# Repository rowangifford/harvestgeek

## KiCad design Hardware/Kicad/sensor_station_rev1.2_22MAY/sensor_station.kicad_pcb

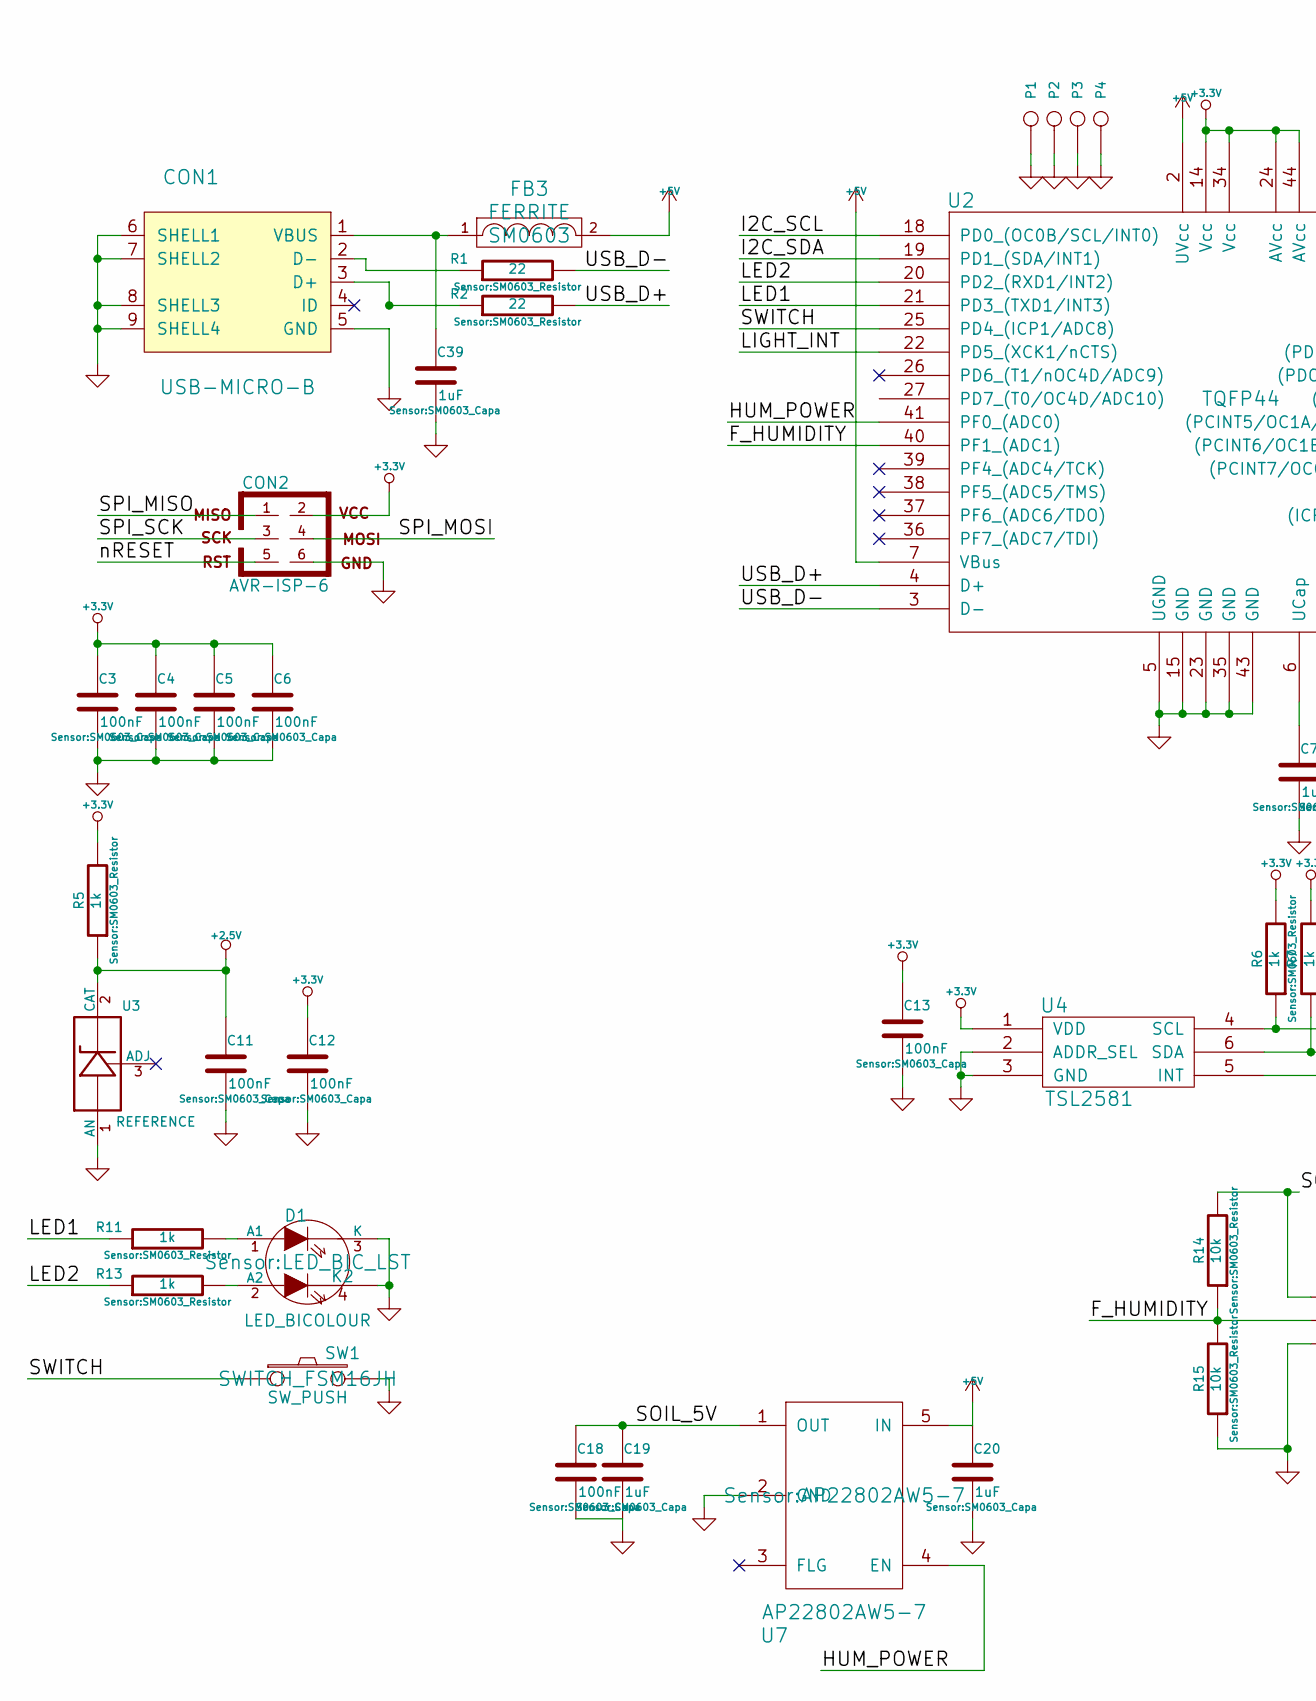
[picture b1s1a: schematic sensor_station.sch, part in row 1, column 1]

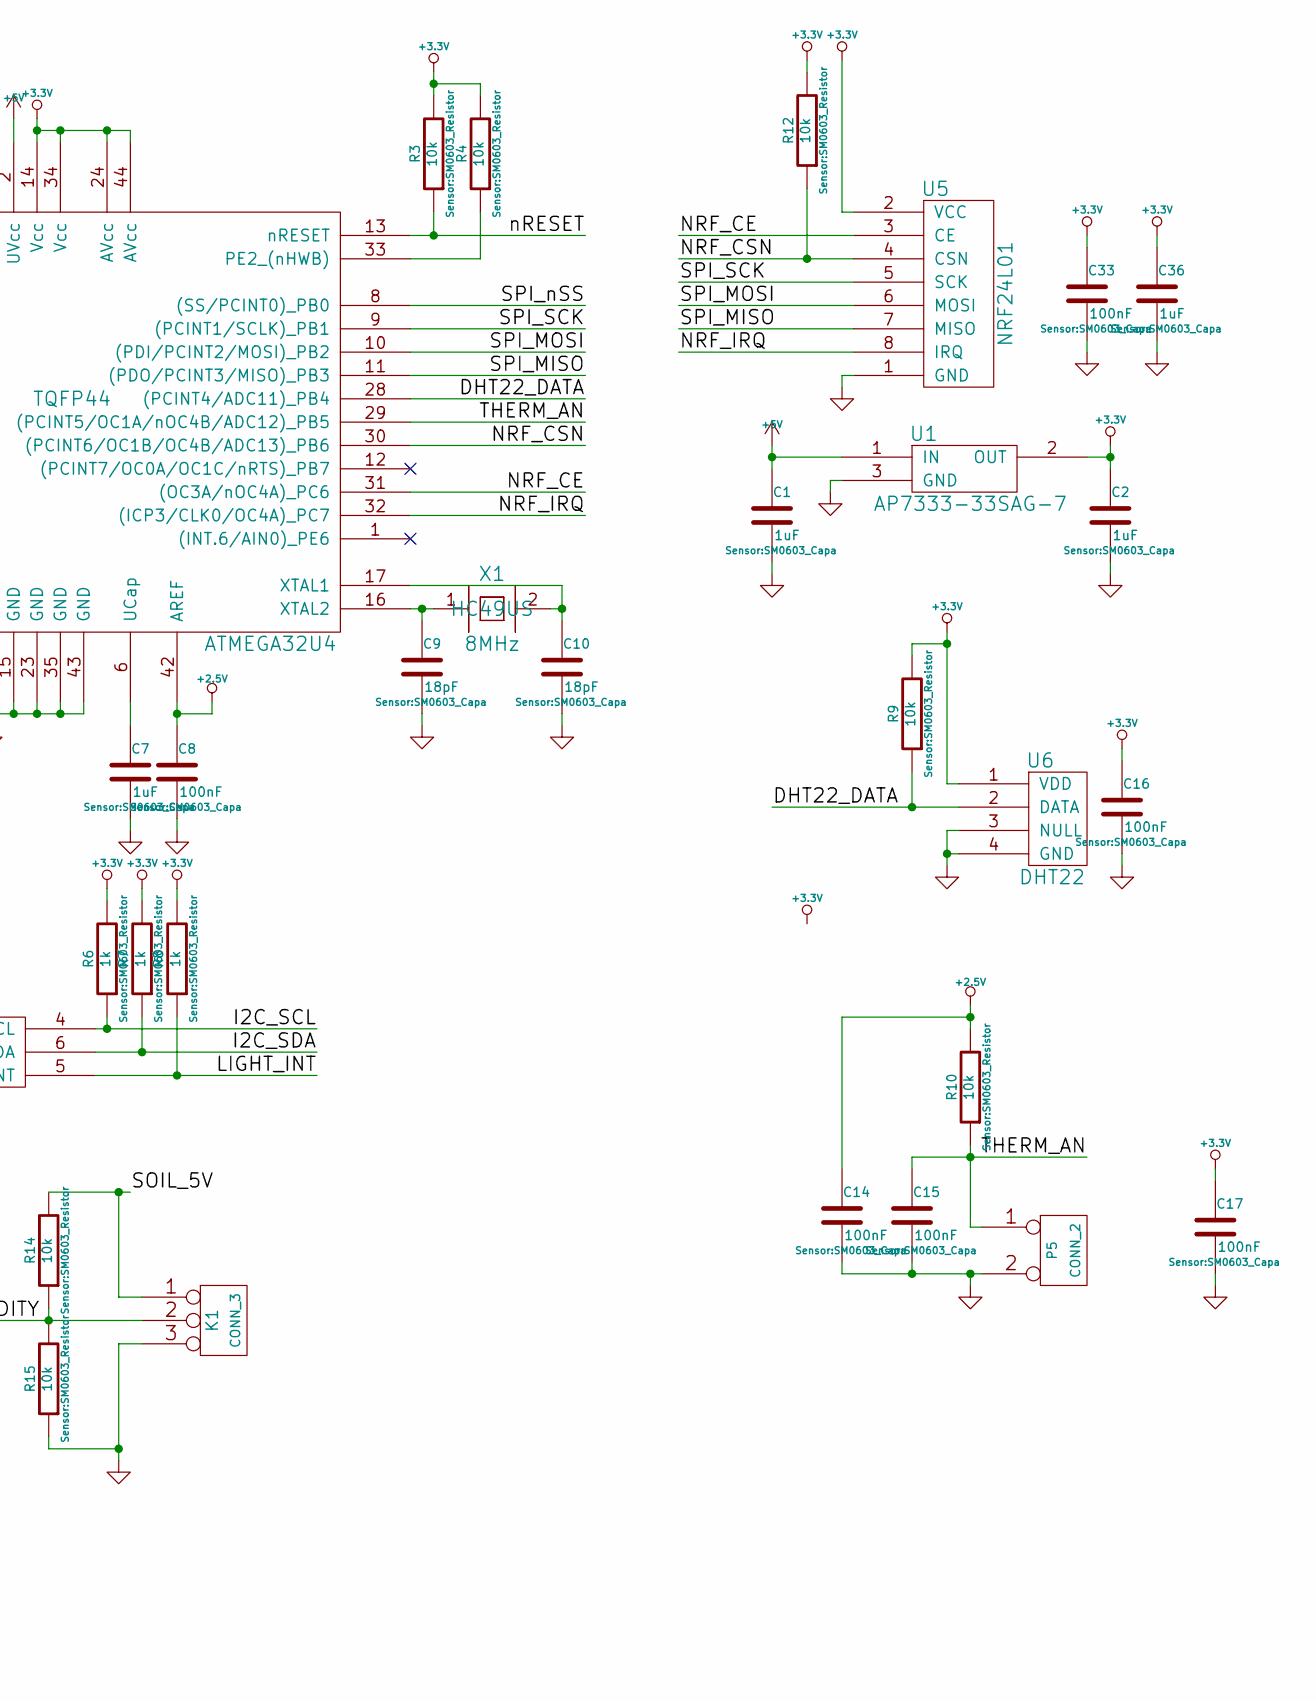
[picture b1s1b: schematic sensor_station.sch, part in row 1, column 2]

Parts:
C1, C2, C7, C19, C20, C36, C39: 1uF; SM0603_Capa
C3, C4, C5, C6, C8, C11, C12, C13, C14, C15, C16, C17, C18, C33: 100nF; SM0603_Capa
C9, C10: 18pF; SM0603_Capa
CON1: USB-MICRO-B; con_microusb_10103594
CON2: AVR-ISP-6; pin_array_3x2
D1: LED_BICOLOUR; LED_BIC_LST
FB3: FERRITE; SM0603
K1: CONN_3; CON_3_weidmuller
P1, P2, P3, P4: CONN_1; HOLE_FIX_HAMMOND
P5: CONN_2; CON_2_weidmuller
R1, R2: 22; SM0603_Resistor
R3, R4, R9, R10, R12, R14, R15: 10k; SM0603_Resistor
R5, R6, R7, R8, R11, R13: 1k; SM0603_Resistor
SW1: SW_PUSH; SWITCH_FSM16JH
U1: AP7333-33SAG-7; SOT23
U2: ATMEGA32U4; TQFP44
U3: REFERENCE; TO92F
U4: TSL2581; 6-WDFN
U5: NRF24L01
U6: DHT22
U7: AP22802AW5-7
X1: 8MHz; HC49US

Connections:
+2.5V: C8.1, C11.1, C14.1, R5.1, R10.2, U2.42 (AREF), U3.2 (CAT)
+3.3V: C2.1, C3.1, C4.1, C5.1, C6.1, C12.1, C13.1, C16.1, C17.1, C33.1, C36.1, CON2.2, R3.2, R4.2, R5.2, R6.2, R7.2, R8.2, R9.2, R12.2, U1.2 (OUT), U2.14 (Vcc), U2.24 (AVcc), U2.34 (Vcc), U2.44 (AVcc), U4.1 (VDD), U5.2 (VCC), U6.1 (VDD)
+5V: C1.1, C20.1, FB3.2, U1.1 (IN), U2.2 (UVcc), U2.7 (VBus), U7.5 (IN)
/DHT22_DATA: R9.1, U2.28 ((PCINT4/ADC11)_PB4), U6.2 (DATA)
/F_HUMIDITY: K1.2 (PM), R14.1, R15.2, U2.40 (PF1_(ADC1))
/HUM_POWER: U2.41 (PF0_(ADC0)), U7.4 (EN)
/I2C_SCL: R6.1, U2.18 (PD0_(OC0B/SCL/INT0)), U4.4 (SCL)
/I2C_SDA: R7.1, U2.19 (PD1_(SDA/INT1)), U4.6 (SDA)
/LED1: R11.1, U2.21 (PD3_(TXD1/INT3))
/LED2: R13.1, U2.20 (PD2_(RXD1/INT2))
/LIGHT_INT: R8.1, U2.22 (PD5_(XCK1/nCTS)), U4.5 (INT)
/NRF_CE: U2.31 ((OC3A/nOC4A)_PC6), U5.3 (CE)
/NRF_CSN: R12.1, U2.30 ((PCINT6/OC1B/OC4B/ADC13)_PB6), U5.4 (CSN)
/NRF_IRQ: U2.32 ((ICP3/CLK0/OC4A)_PC7), U5.8 (IRQ)
/SOIL_5V: C18.1, C19.1, K1.1, R14.2, U7.1 (OUT)
/SPI_MISO: CON2.1, U2.11 ((PDO/PCINT3/MISO)_PB3), U5.7 (MISO)
/SPI_MOSI: CON2.4, U2.10 ((PDI/PCINT2/MOSI)_PB2), U5.6 (MOSI)
/SPI_SCK: CON2.3, U2.9 ((PCINT1/SCLK)_PB1), U5.5 (SCK)
/SPI_nSS: U2.8 ((SS/PCINT0)_PB0)
/SWITCH: SW1.1, U2.25 (PD4_(ICP1/ADC8))
/THERM_AN: C15.1, P5.1, R10.1, U2.29 ((PCINT5/OC1A/nOC4B/ADC12)_PB5)
/USB_D+: R2.2, U2.4 (D+)
/USB_D-: R1.2, U2.3 (D-)
/nRESET: CON2.5, R3.1, U2.13 (nRESET)
GND: C1.2, C2.2, C3.2, C4.2, C5.2, C6.2, C7.2, C8.2, C9.2, C10.2, C11.2, C12.2, C13.2, C14.2, C15.2, C16.2, C17.2, C18.2, C19.2, C20.2, C33.2, C36.2, C39.2, CON1.5 (GND), CON1.6 (SHELL1), CON1.7 (SHELL2), CON1.8 (SHELL3), CON1.9 (SHELL4), CON2.6, D1.3 (K), D1.4 (K2), K1.3, P1.1, P2.1, P3.1, P4.1, P5.2 (PM), R15.1, SW1.2, U1.3 (GND), U2.5 (UGND), U2.15 (GND), U2.23 (GND), U2.35 (GND), U2.43 (GND), U3.1 (AN), U4.2 (ADDR_SEL), U4.3 (GND), U5.1 (GND), U6.3 (NULL), U6.4 (GND), U7.2 (GND); also elsewhere on the board
unnamed: C7.1, U2.6 (UCap)
unnamed: C9.1, U2.16 (XTAL2), X1.1
unnamed: C10.1, U2.17 (XTAL1), X1.2
unnamed: C39.1, CON1.1 (VBUS), FB3.1
unnamed: CON1.2 (D-), R1.1
unnamed: CON1.3 (D+), R2.1
unnamed: D1.1 (A1), R11.2
unnamed: D1.2 (A2), R13.2
unnamed: R4.1, U2.33 (PE2_(nHWB))

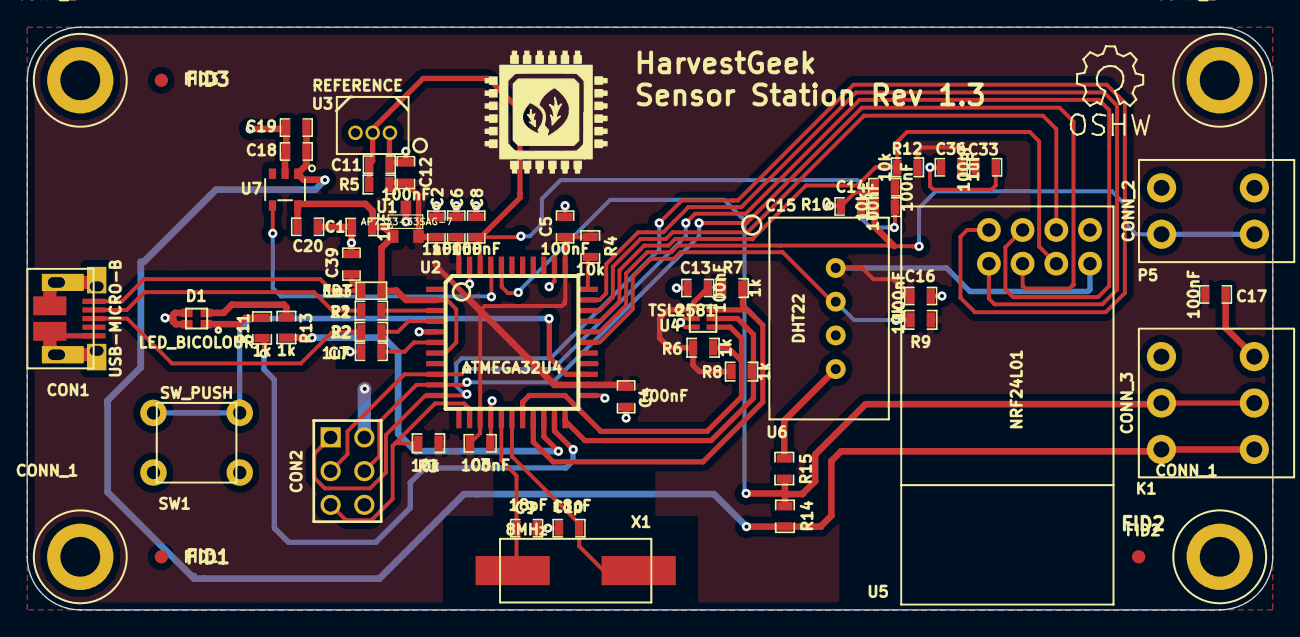
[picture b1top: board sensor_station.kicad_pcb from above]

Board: 2 copper layers, 93.9 x 43.9 mm, 60 parts (0 on the bottom side), 33 nets.

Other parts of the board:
Fiducial: FID3; Fiducial
Fiducial#2: FID2; Fiducial
Fiducial#3: FID1; Fiducial
P1#2, P1#3, P1#4: CONN_1; HOLE_FIX_HAMMOND

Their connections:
GND: P1#2.1, P1#3.1, P1#4.1; also elsewhere on the board

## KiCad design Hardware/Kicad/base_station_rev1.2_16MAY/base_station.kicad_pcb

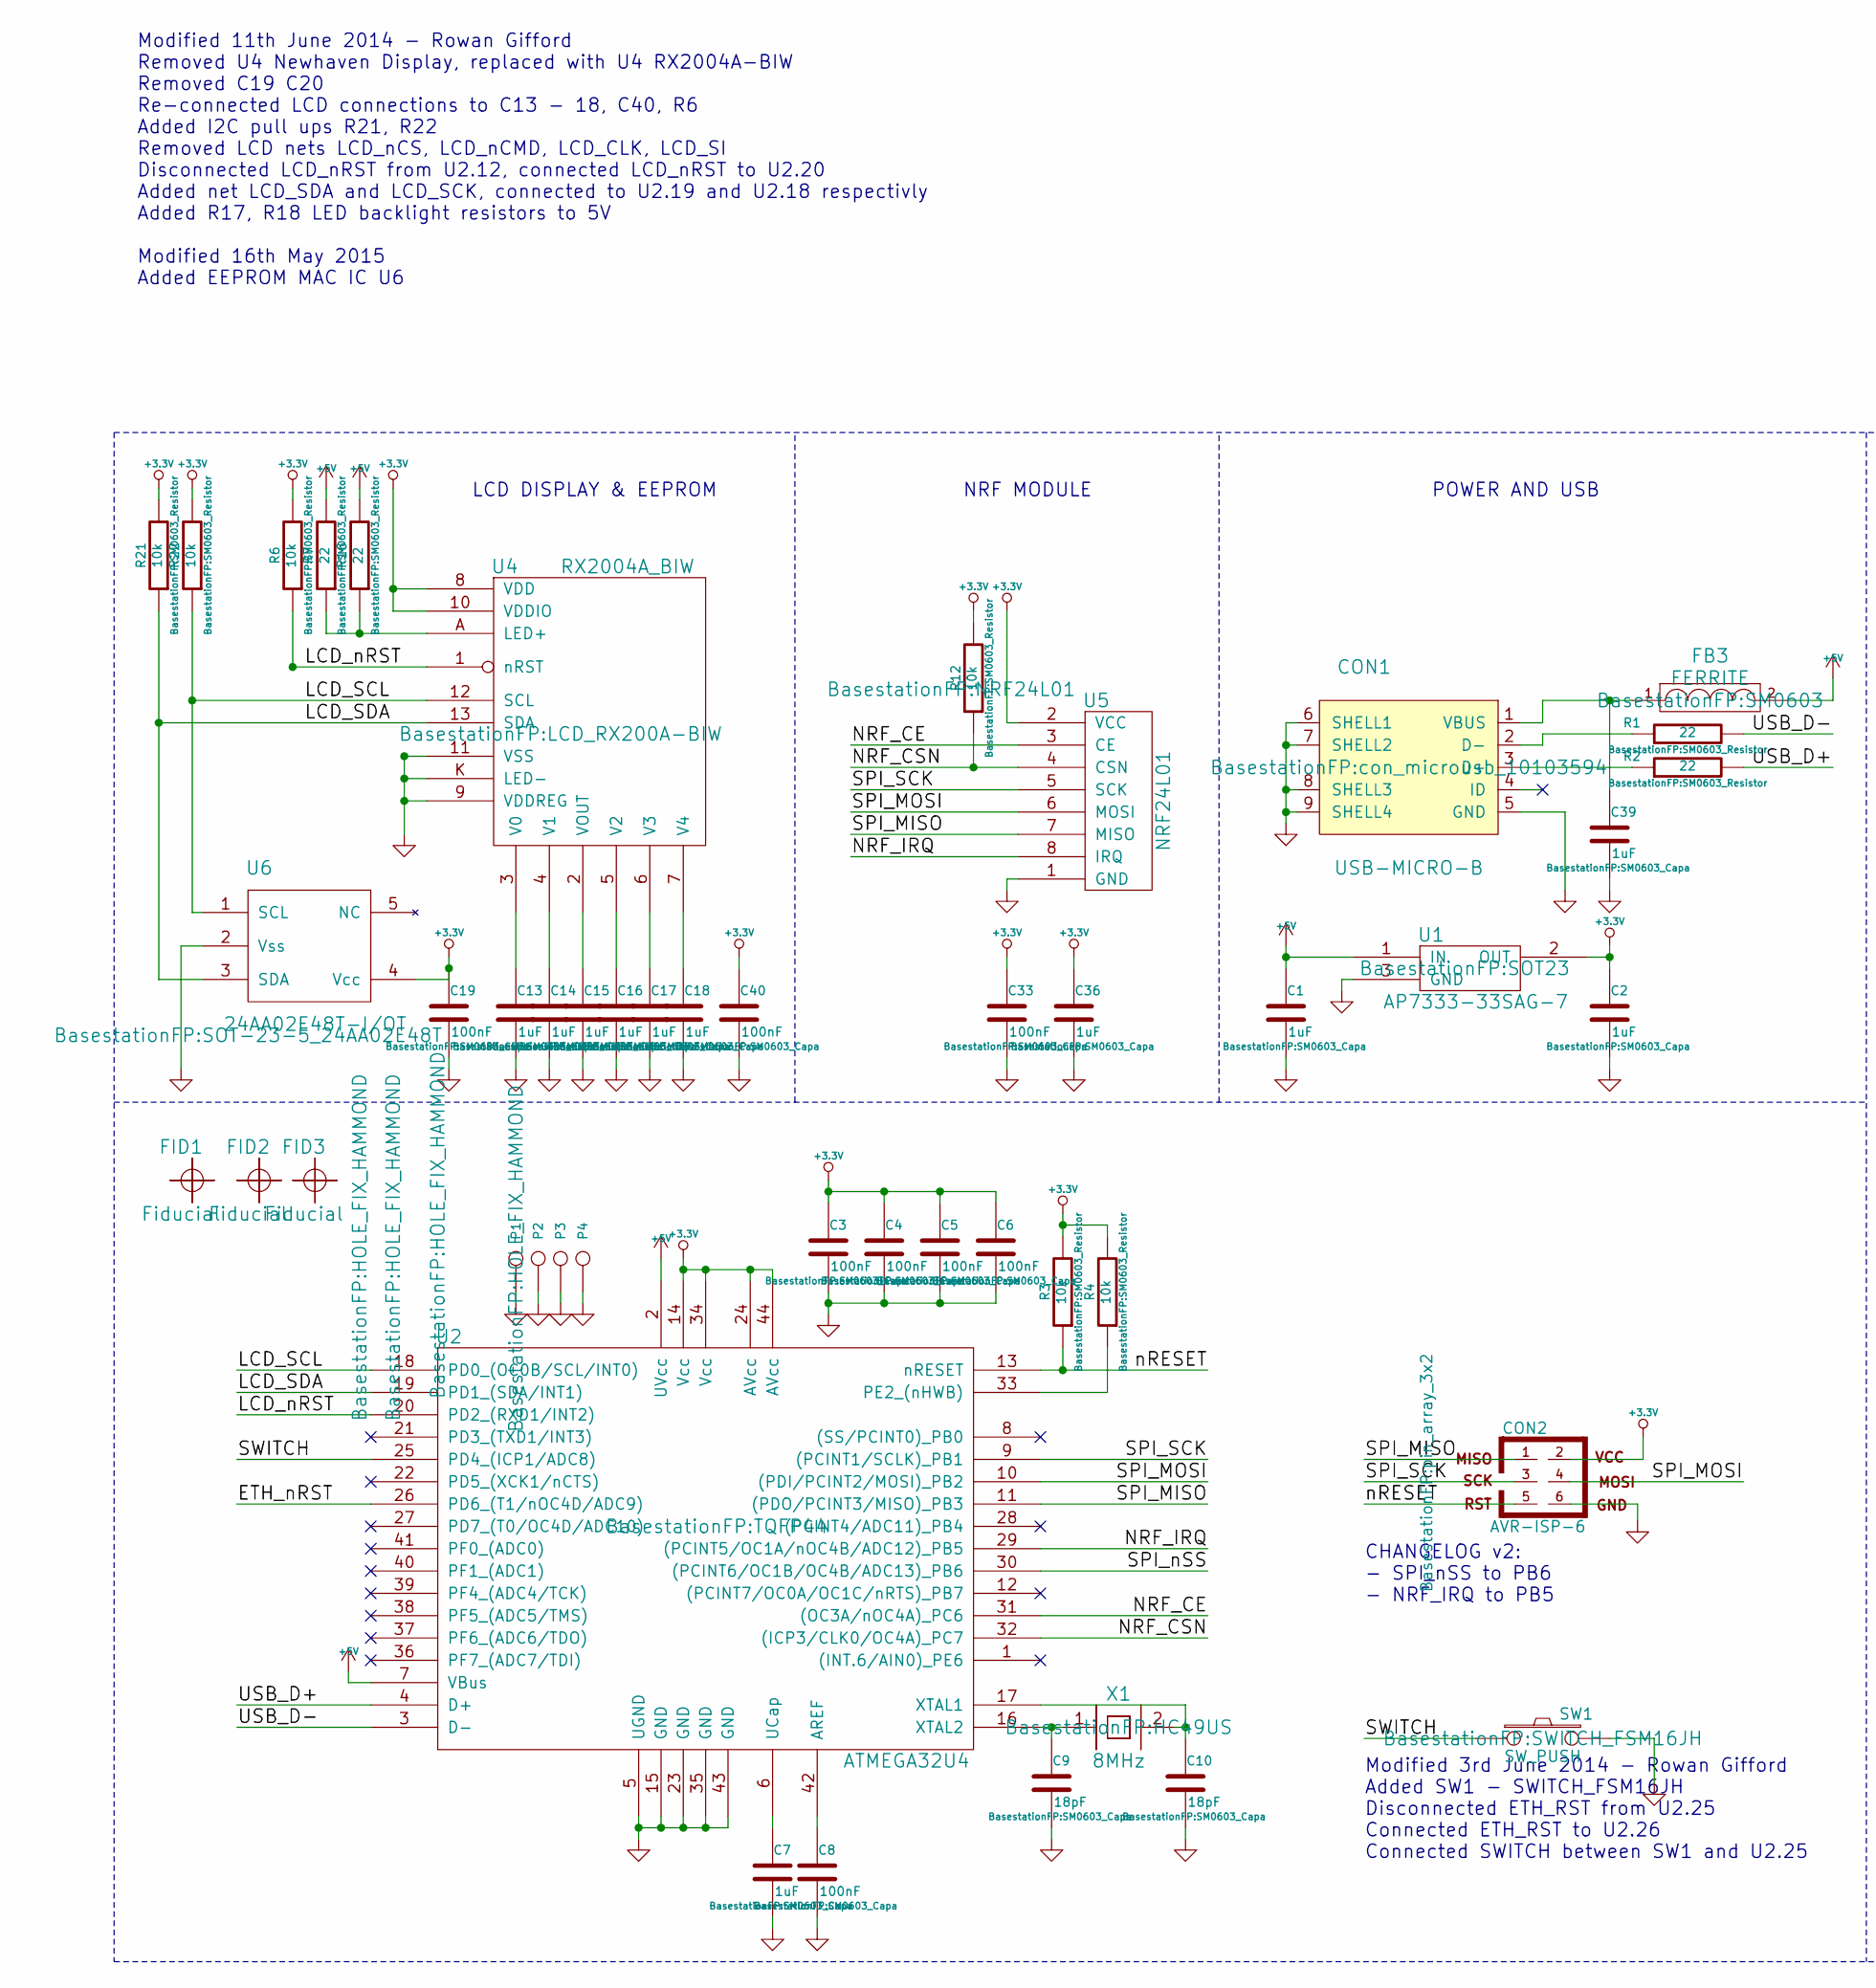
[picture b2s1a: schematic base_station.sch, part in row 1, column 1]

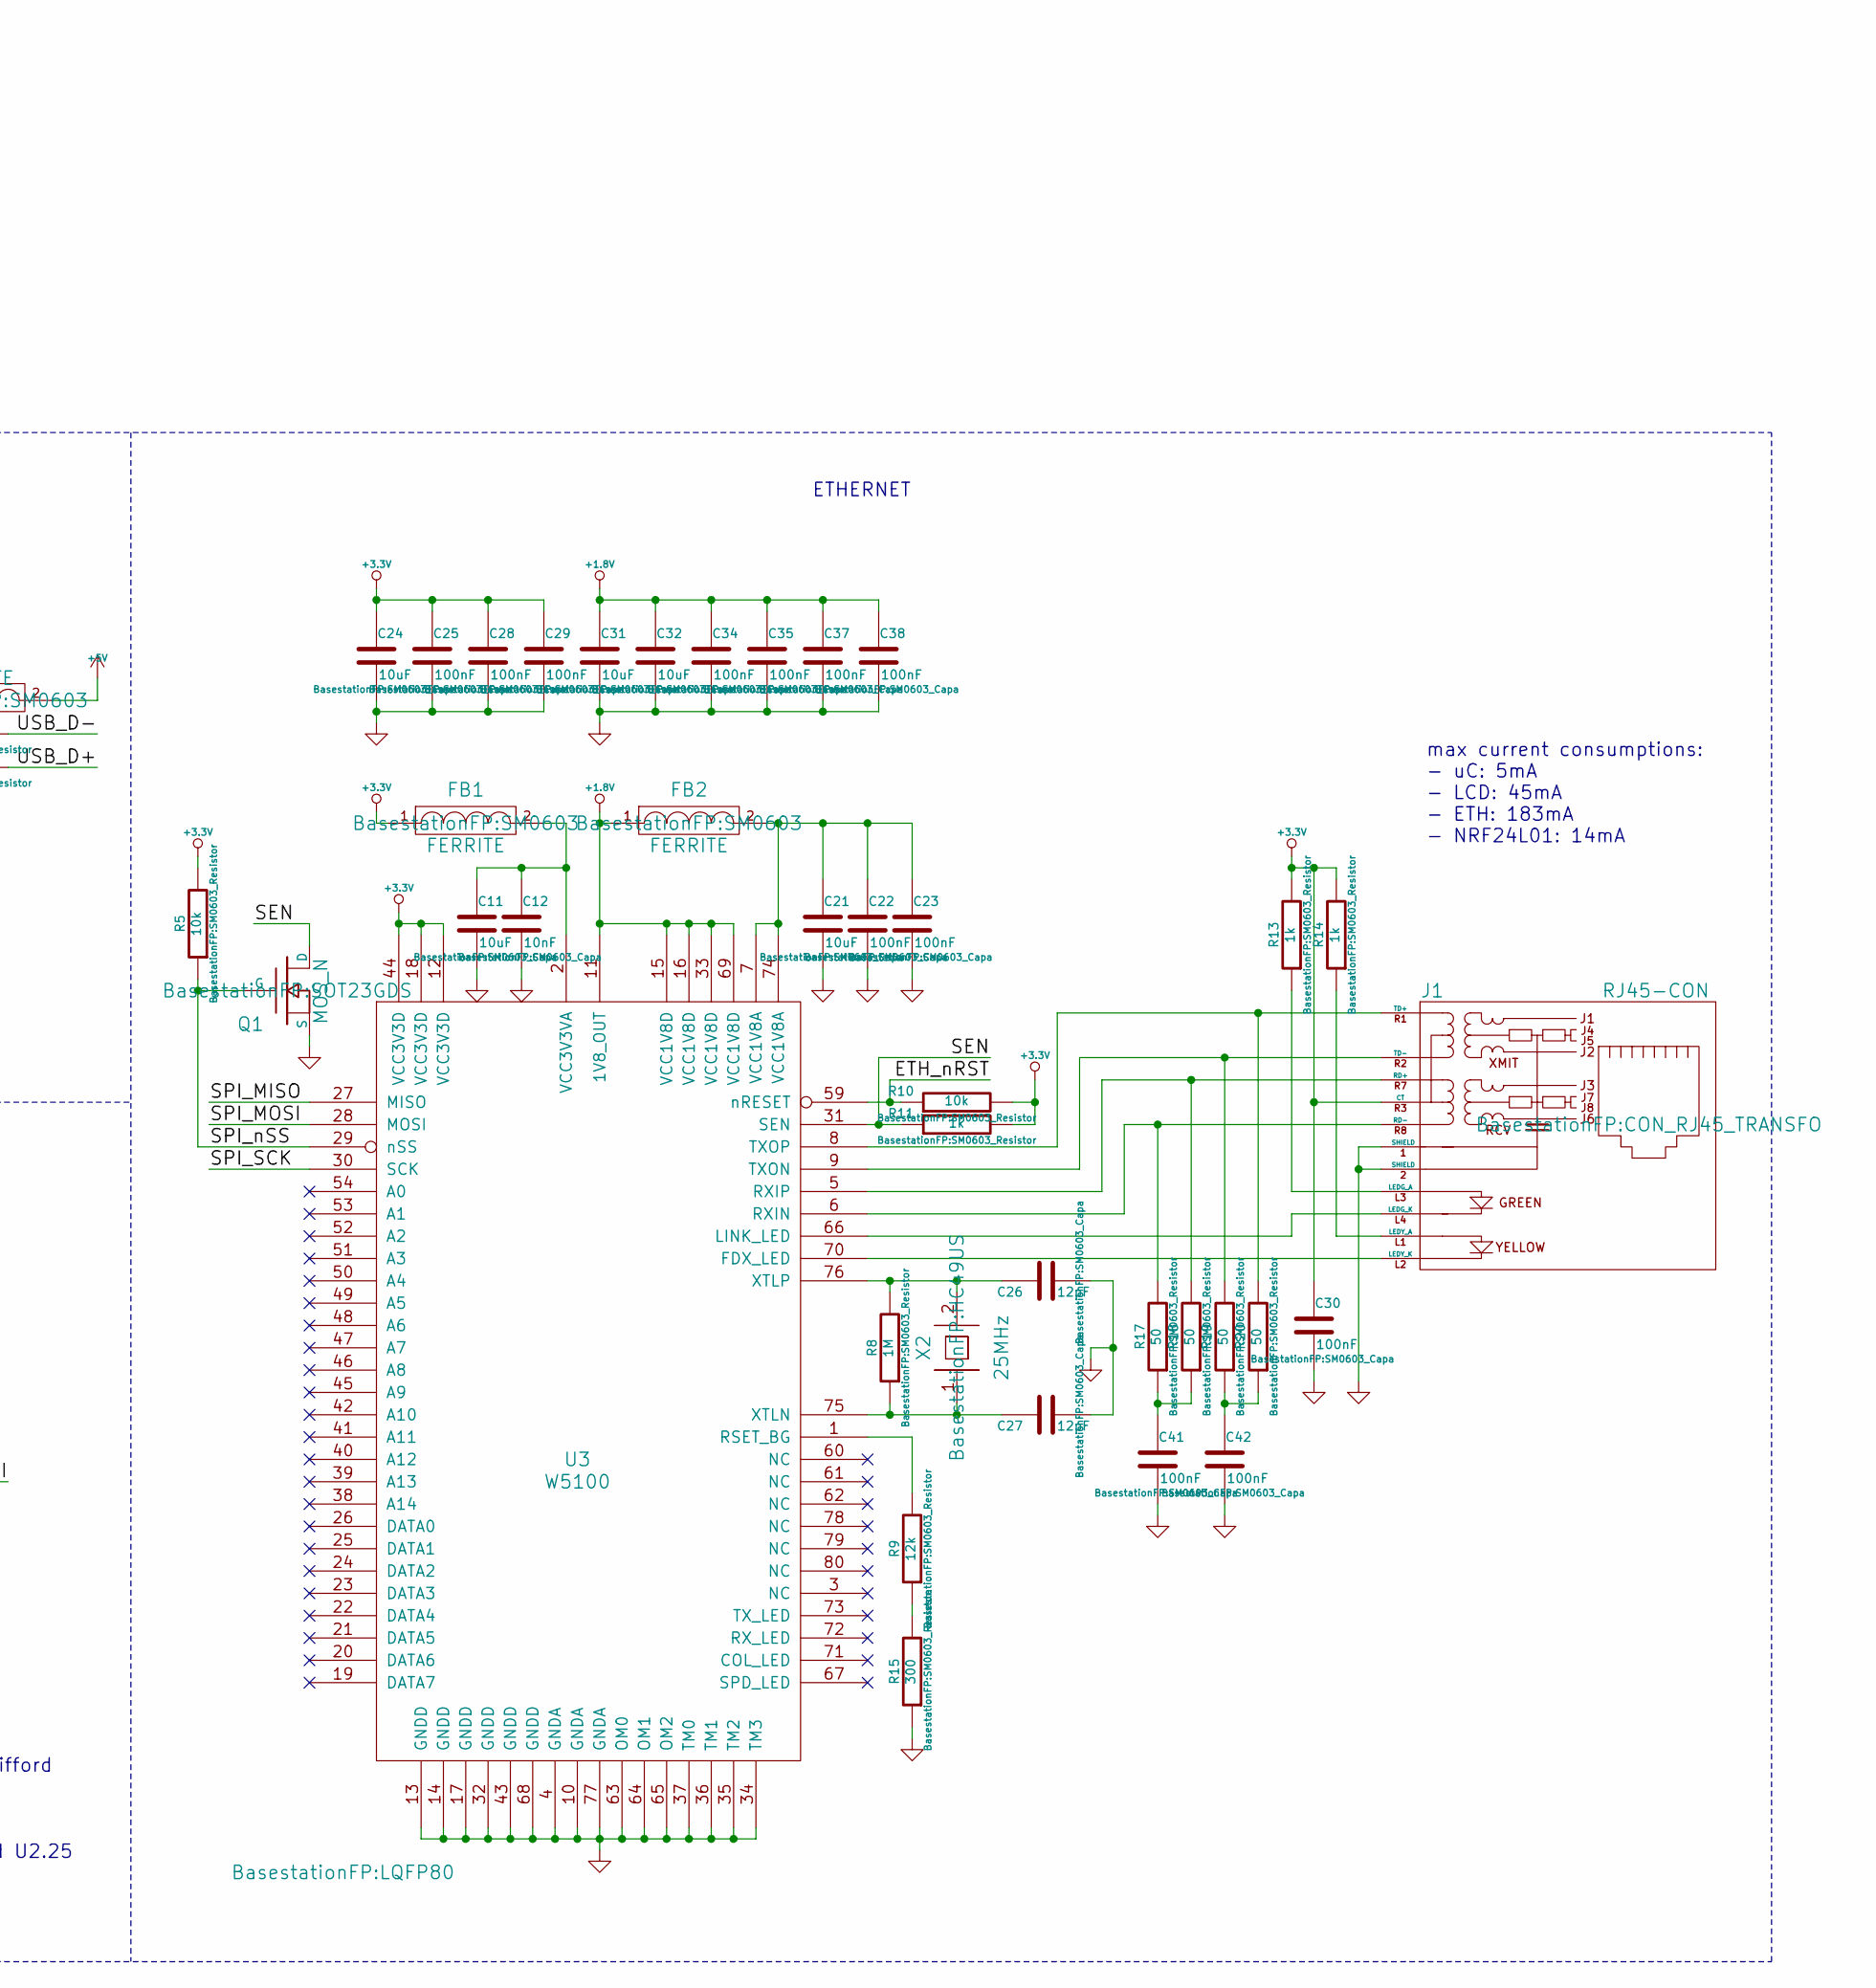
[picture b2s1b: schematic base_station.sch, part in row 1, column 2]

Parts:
C1, C2, C7, C13, C14, C15, C16, C17, C18, C36, C39: 1uF; SM0603_Capa
C3, C4, C5, C6, C8, C19, C22, C23, C25, C28, C29, C30, C33, C34, C35, C37, C38, C40, C41, C42: 100nF; SM0603_Capa
C9, C10: 18pF; SM0603_Capa
C11, C21, C24, C31, C32: 10uF; SM0603_Capa
C12: 10nF; SM0603_Capa
C26, C27: 12pF; SM0603_Capa
CON1: USB-MICRO-B; con_microusb_10103594
CON2: AVR-ISP-6; pin_array_3x2
FB1, FB2, FB3: FERRITE; SM0603
FID1, FID2, FID3: Fiducial
J1: RJ45-CON; CON_RJ45_TRANSFO
P1, P2, P3, P4: CONN_1; HOLE_FIX_HAMMOND
Q1: MOS_N; SOT23GDS
R1, R2, R7, R16: 22; SM0603_Resistor
R3, R4, R5, R6, R10, R12, R21, R22: 10k; SM0603_Resistor
R8: 1M; SM0603_Resistor
R9: 12k; SM0603_Resistor
R11, R13, R14: 1k; SM0603_Resistor
R15: 300; SM0603_Resistor
R17, R18, R19, R20: 50; SM0603_Resistor
SW1: SW_PUSH; SWITCH_FSM16JH
U1: AP7333-33SAG-7; SOT23
U2: ATMEGA32U4; TQFP44
U3: W5100; LQFP80
U4: RX2004A_BIW; LCD_RX200A-BIW
U5: NRF24L01
U6: 24AA02E48T-I/OT; SOT-23-5_24AA02E48T
X1: 8MHz; HC49US
X2: 25MHz; HC49US

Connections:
+1.8V: C31.1, C32.1, C34.1, C35.1, C37.1, C38.1, FB2.1, U3.11 (1V8_OUT), U3.15 (VCC1V8D), U3.16 (VCC1V8D), U3.33 (VCC1V8D), U3.69 (VCC1V8D)
+3.3V: C2.1, C3.1, C4.1, C5.1, C6.1, C19.1, C24.1, C25.1, C28.1, C29.1, C30.1, C33.1, C36.1, C40.1, CON2.2, FB1.1, J1.R3 (CT), R3.2, R4.2, R5.2, R6.2, R10.2, R11.2, R12.2, R13.2, R14.2, R21.2, R22.2, U1.2 (OUT), U2.14 (Vcc), U2.24 (AVcc), U2.34 (Vcc), U2.44 (AVcc), U3.12 (VCC3V3D), U3.18 (VCC3V3D), U3.44 (VCC3V3D), U4.8 (VDD), U4.10 (VDDIO), U5.2 (VCC), U6.4 (Vcc)
+5V: C1.1, FB3.2, R7.2, R16.2, U1.1 (IN), U2.2 (UVcc), U2.7 (VBus)
/ETH_nRST: R10.1, U2.26 (PD6_(T1/nOC4D/ADC9)), U3.59 (nRESET)
/LCD_SCL: R22.1, U2.18 (PD0_(OC0B/SCL/INT0)), U4.12 (SCL), U6.1 (SCL)
/LCD_SDA: R21.1, U2.19 (PD1_(SDA/INT1)), U4.13 (SDA), U6.3 (SDA)
/LCD_nRST: R6.1, U2.20 (PD2_(RXD1/INT2)), U4.1 (nRST)
/NRF_CE: U2.31 ((OC3A/nOC4A)_PC6), U5.3 (CE)
/NRF_CSN: R12.1, U2.32 ((ICP3/CLK0/OC4A)_PC7), U5.4 (CSN)
/NRF_IRQ: U2.29 ((PCINT5/OC1A/nOC4B/ADC12)_PB5), U5.8 (IRQ)
/SEN: Q1.D, R11.1, U3.31 (SEN)
/SPI_MISO: CON2.1, U2.11 ((PDO/PCINT3/MISO)_PB3), U3.27 (MISO), U5.7 (MISO)
/SPI_MOSI: CON2.4, U2.10 ((PDI/PCINT2/MOSI)_PB2), U3.28 (MOSI), U5.6 (MOSI)
/SPI_SCK: CON2.3, U2.9 ((PCINT1/SCLK)_PB1), U3.30 (SCK), U5.5 (SCK)
/SPI_nSS: Q1.G, R5.1, U2.30 ((PCINT6/OC1B/OC4B/ADC13)_PB6), U3.29 (nSS)
/SWITCH: SW1.1, U2.25 (PD4_(ICP1/ADC8))
/USB_D+: R2.2, U2.4 (D+)
/USB_D-: R1.2, U2.3 (D-)
/nRESET: CON2.5, R3.1, U2.13 (nRESET)
GND: C1.2, C2.2, C3.2, C4.2, C5.2, C6.2, C7.2, C8.2, C9.2, C10.2, C11.2, C12.2, C13.2, C14.2, C15.2, C16.2, C17.2, C18.2, C19.2, C21.2, C22.2, C23.2, C24.2, C25.2, C26.2, C27.2, C28.2, C29.2, C30.2, C31.2, C32.2, C33.2, C34.2, C35.2, C36.2, C37.2, C38.2, C39.2, C40.2, C41.2, C42.2, CON1.5 (GND), CON1.6 (SHELL1), CON1.7 (SHELL2), CON1.8 (SHELL3), CON1.9 (SHELL4), CON2.6, J1.1 (SHIELD), J1.2 (SHIELD), P1.1, P2.1, P3.1, P4.1, Q1.S, R15.1, SW1.2, U1.3 (GND), U2.5 (UGND), U2.15 (GND), U2.23 (GND), U2.35 (GND), U2.43 (GND), U3.4 (GNDA), U3.10 (GNDA), U3.13 (GNDD), U3.14 (GNDD), U3.17 (GNDD), U3.32 (GNDD), U3.34 (TM3), U3.35 (TM2), U3.36 (TM1), U3.37 (TM0), U3.43 (GNDD), U3.63 (OM0), U3.64 (OM1), U3.65 (OM2), U3.68 (GNDD), U3.77 (GNDA), U4.9 (VDDREG), U4.11 (VSS), U4.K (LED-), U5.1 (GND), U6.2 (Vss)
unnamed: C7.1, U2.6 (UCap)
unnamed: C8.1, U2.42 (AREF)
unnamed: C9.1, U2.16 (XTAL2), X1.1
unnamed: C10.1, U2.17 (XTAL1), X1.2
unnamed: C11.1, C12.1, FB1.2, U3.2 (VCC3V3VA)
unnamed: C13.1, U4.3 (V0)
unnamed: C14.1, U4.4 (V1)
unnamed: C15.1, U4.2 (VOUT)
unnamed: C16.1, U4.5 (V2)
unnamed: C17.1, U4.6 (V3)
unnamed: C18.1, U4.7 (V4)
unnamed: C21.1, C22.1, C23.1, FB2.2, U3.7 (VCC1V8A), U3.74 (VCC1V8A)
unnamed: C26.1, R8.2, U3.76 (XTLP), X2.2
unnamed: C27.1, R8.1, U3.75 (XTLN), X2.1
unnamed: C39.1, CON1.1 (VBUS), FB3.1
unnamed: C41.1, R17.1, R18.1
unnamed: C42.1, R19.1, R20.1
unnamed: CON1.2 (D-), R1.1
unnamed: CON1.3 (D+), R2.1
unnamed: J1.L1 (LEDY_A), R14.1
unnamed: J1.L2 (LEDY_K), U3.70 (FDX_LED)
unnamed: J1.L3 (LEDG_A), R13.1
unnamed: J1.L4 (LEDG_K), U3.66 (LINK_LED)
unnamed: J1.R1 (TD+), R20.2, U3.8 (TXOP)
unnamed: J1.R2 (TD-), R19.2, U3.9 (TXON)
unnamed: J1.R7 (RD+), R18.2, U3.5 (RXIP)
unnamed: J1.R8 (RD-), R17.2, U3.6 (RXIN)
unnamed: R4.1, U2.33 (PE2_(nHWB))
unnamed: R9.2, U3.1 (RSET_BG)
unnamed: R9.1, R15.2
unnamed: R7.1, R16.1, U4.A (LED+)

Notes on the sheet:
max current consumptions: - uC: 5mA - LCD: 45mA - ETH: 183mA - NRF24L01: 14mA
LCD DISPLAY & EEPROM
NRF MODULE
POWER AND USB
ETHERNET
CHANGELOG v2: - SPI_nSS to PB6 - NRF_IRQ to PB5
Modified 3rd June 2014 - Rowan Gifford Added SW1 - SWITCH_FSM16JH Disconnected ETH_RST from U2.25 Connected ETH_RST to U2.26 Connected SWITCH between SW1 and U2.25
Modified 11th June 2014 - Rowan Gifford Removed U4 Newhaven Display, replaced with U4 RX2004A-BIW Removed C19 C20 Re-connected LCD connections to C13 - 18, C40, R6 Added I2C pull ups R21, R22 Removed LCD nets LCD_nCS, LCD_nCMD, LCD_CLK, LCD_SI Disconnected LCD_nRST from U2.12, connected LCD_nRST to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

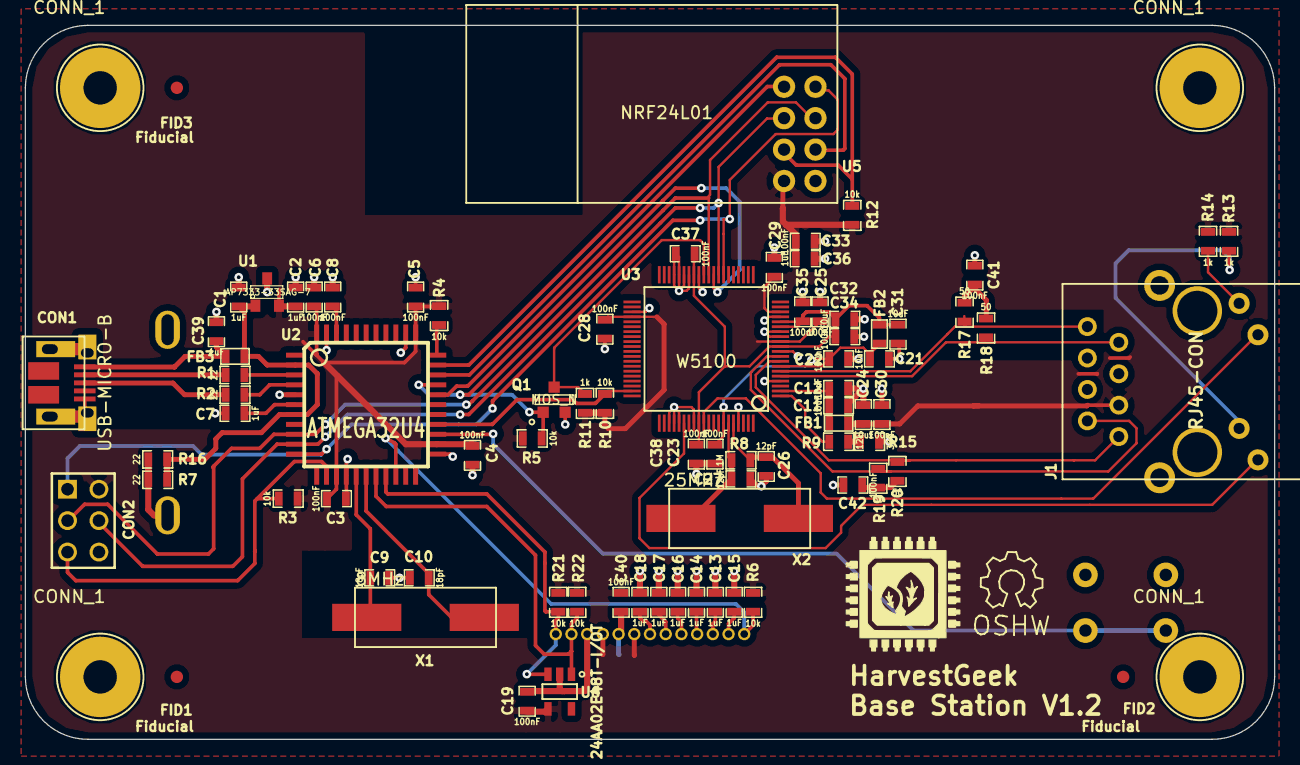
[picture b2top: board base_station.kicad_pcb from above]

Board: 2 copper layers, 101.0 x 57.7 mm, 86 parts (0 on the bottom side), 51 nets.

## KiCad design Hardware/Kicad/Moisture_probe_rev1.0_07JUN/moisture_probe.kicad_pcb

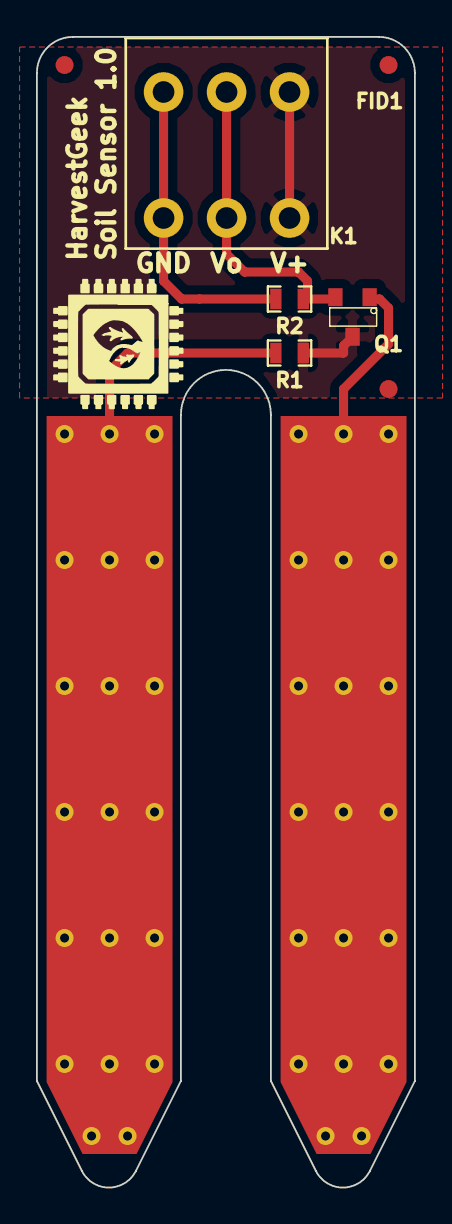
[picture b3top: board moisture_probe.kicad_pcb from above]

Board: 2 copper layers, 21.0 x 63.9 mm, 9 parts (0 on the bottom side), 5 nets.

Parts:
Fiducial: FID1; Fiducial
Fiducial#2, Fiducial#3: FID1; Fiducial
K1: CONN_3; CON_3_weidmuller
P1, P2: CONN_01X01; probe
Q1: MMBT2222ALT3G; SOT23
R1, R2: 100R; SM0603_Resistor

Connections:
unnamed: K1.1, Q1.3, R1.2
unnamed: K1.2, Q1.2, R2.2
unnamed: K1.3, R2.1
unnamed: P1.1, Q1.1
unnamed: P2.1, R1.1

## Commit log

2015-05-11 Initial commit RG
2015-05-11 Initial commit RG2
2015-05-16 Add kikcad
2015-05-17 Modified HW - BS gerbers
2015-05-22 Sensor Station PCB updates
2015-05-22 Sensor Station PCB updates2
2015-05-23 Added manufacturing files
2015-05-29 Latest manufacturing outputs
2015-06-23 23/06/2015 RG
